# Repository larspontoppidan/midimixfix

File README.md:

# MidiMixFix

*Now open source!*

Midimixfix is a standalone MIDI processing unit with custom designed electronics and software for mixing and processing streams of MIDI.

## Features at a glance

- Two MIDI inputs and one MIDI output.
- Two pedal inputs assignable to MIDI controllers.
- All inputs can have their MIDI channels filtered, reassigned, merged or individually processed very flexibly. MIDI messages can be modified and generated.
- Midimixfix is independent of a PC. Configuration is done using the buttons and display.
- Transformation of continuous MIDI message values based on configurable curves.
- Splitting of polyphony into seperate monophonic MIDI channels for control of individual notes.
- Aftertouch processing, smoothing and reassignment to other controllers.
- Conditional processing based on triggers or keyboard split.
- Analysis of MIDI data with the MIDI logger feature.
- Save/Load of configuration presets. One preset is loaded at start up.
- Software in Midimixfix can be upgraded using the USB connection.

## Links

Read more here: https://larsee.com/blog/tag/midimixfix.html

Youtube video demonstrations:
- [Midimixfix demonstration, fixing key velocity using curve filter](https://www.youtube.com/watch?v=JRt7MXFQuEk)
- [Vibrato Pedal on a Piano? Enhancing Rachmaninoff with Midimixfix](https://www.youtube.com/watch?v=KIDRwiXo5tw)
- [Polyphonic aftertouch effects with Midimixfix channel split feature](https://www.youtube.com/watch?v=yqUHe00-khM)

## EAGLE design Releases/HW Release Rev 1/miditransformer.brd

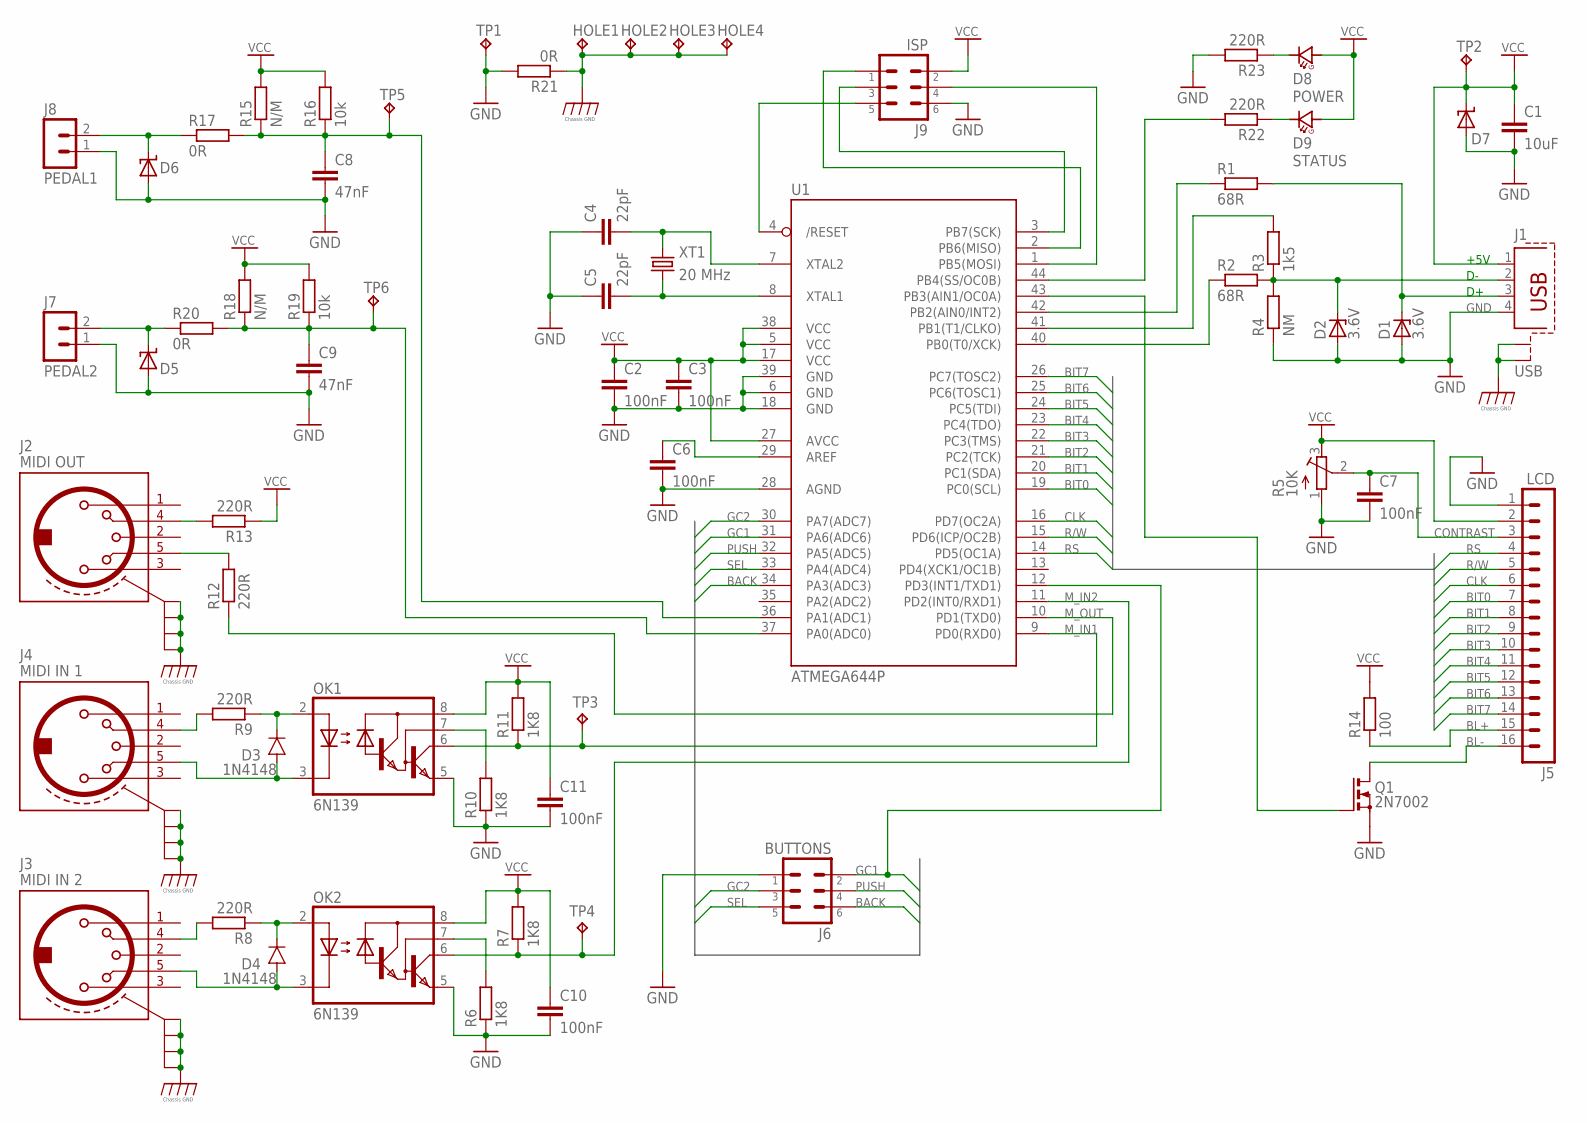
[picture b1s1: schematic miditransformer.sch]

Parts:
C1: 10uF; C1210
C2, C3, C6, C7, C10, C11: 100nF; C0805
C4, C5: 22pF; C0805
C8, C9: 47nF; C0805
D1, D2: 3.6V; DO34Z7
D3, D4: 1N4148; MINIMELF
D5, D6, D7: SUPPRESSOR-SMB; SMB
D8: POWER; LED3MM
D9: STATUS; LED3MM
HOLE1, HOLE2, HOLE3, HOLE4: HOLE_PAD; HOLE_PAD_3.2
J1: USB; PN61729-S
J2: MIDI OUT; DIN5_FEM_UNIV
J3: MIDI IN 2; DIN5_FEM_UNIV
J4: MIDI IN 1; DIN5_FEM_UNIV
J5: LCD; HDR_S_2X8
J6: BUTTONS; HDR_S_2X3
J7: PEDAL2; MOLEX_KK_HDR2_FL
J8: PEDAL1; MOLEX_KK_HDR2_FL
J9: ISP; HDR_2X3
OK1, OK2: 6N139; DIL08
Q1: 2N7002; SOT23
R1, R2: 68R; R0805
R3: 1k5; R0805
R4: NM; R0805
R5: 10K; RTRIM3339P
R6, R7, R10, R11: 1K8; R0805
R8, R9, R12, R13, R22, R23: 220R; R0805
R14: 100; 0207/7
R15, R18: N/M; R0805
R16, R19: 10k; R0805
R17, R20, R21: 0R; R0805
TP1, TP2, TP3, TP4, TP5, TP6: TPTH-15-06; TP-TH-15-06
U1: ATMEGA644P; TQFP44
XT1: 20 MHz; HC49

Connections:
BACK: J6.6, U1.34 (PA3(ADC3))
BIT0: J5.7, U1.19 (PC0(SCL))
BIT1: J5.8, U1.20 (PC1(SDA))
BIT2: J5.9, U1.21 (PC2(TCK))
BIT3: J5.10, U1.22 (PC3(TMS))
BIT4: J5.11, U1.23 (PC4(TDO))
BIT5: J5.12, U1.24 (PC5(TDI))
BIT6: J5.13, U1.25 (PC6(TOSC1))
BIT7: J5.14, U1.26 (PC7(TOSC2))
BL+: J5.15, R14.1
BL-: J5.16, Q1.3 (D)
CLK: J5.6, U1.16 (PD7(OC2A))
CONTRAST: C7.1, J5.3, R5.2 (S)
GC1: J6.2, U1.12 (PD3(INT1/TXD1)), U1.31 (PA6(ADC6))
GC2: J6.3, U1.30 (PA7(ADC7))
GND: C1.2, C2.2, C3.2, C4.1, C5.1, C6.2, C7.2, C8.2, C9.2, C10.2, C11.2, D1.A, D2.A, D5.A, D6.A, D7.A, J1.4, J5.1, J6.1, J7.1, J8.1, J9.6, OK1.5 (GND), OK2.5 (GND), Q1.2 (S), R4.1, R5.1 (E), R6.1, R10.1, R21.2, R23.2, TP1.1, U1.6 (GND), U1.18 (GND), U1.28 (AGND), U1.39 (GND)
M_IN1: OK1.6 (VO), R11.1, TP3.1, U1.9 (PD0(RXD0))
M_IN2: OK2.6 (VO), R7.1, TP4.1, U1.11 (PD2(INT0/RXD1))
M_OUT: R12.1, U1.10 (PD1(TXD0))
unnamed: D1.C, J1.3, R1.2
unnamed: D2.C, J1.2, R2.2, R3.1, R4.2
unnamed: R1.1, U1.42 (PB2(AIN0/INT2))
unnamed: R2.1, U1.40 (PB0(T0/XCK))
unnamed: C5.2, U1.8 (XTAL1), XT1.2
unnamed: R3.2, U1.41 (PB1(T1/CLKO))
unnamed: C4.2, U1.7 (XTAL2), XT1.1
unnamed: D9.C, R22.1
unnamed: OK2.7 (VB), R6.2
unnamed: J9.5, U1.4 (/RESET)
unnamed: J9.1, U1.2 (PB6(MISO))
unnamed: J9.3, U1.3 (PB7(SCK))
unnamed: J9.4, U1.1 (PB5(MOSI))
unnamed: D3.A, J4.5, OK1.3 (C)
unnamed: D4.C, OK2.2 (A), R8.1
unnamed: D8.C, R23.1
unnamed: J3.4, R8.2
unnamed: D4.A, J3.5, OK2.3 (C)
unnamed: OK1.7 (VB), R10.2
unnamed: R22.2, U1.44 (PB4(SS/OC0B))
unnamed: Q1.1 (G), U1.43 (PB3(AIN1/OC0A))
unnamed: D3.C, OK1.2 (A), R9.1
unnamed: D6.C, J8.2, R17.1
unnamed: J4.4, R9.2
unnamed: J2.4, R13.2
unnamed: J2.5, R12.2
unnamed: D5.C, J7.2, R20.1
unnamed: C6.1, U1.29 (AREF)
unnamed: C9.1, R18.1, R19.1, R20.2, TP6.1, U1.37 (PA0(ADC0))
unnamed: C8.1, R15.1, R16.1, R17.2, TP5.1, U1.36 (PA1(ADC1))
P$1: HOLE1.P$0, HOLE2.P$0, HOLE3.P$0, HOLE4.P$0, J1.S1, J1.S2, J2.PE@1 (PE), J2.PE@2 (PE), J2.PE@3 (PE), J2.PE@4 (PE), J3.PE@1 (PE), J3.PE@2 (PE), J3.PE@3 (PE), J3.PE@4 (PE), J4.PE@1 (PE), J4.PE@2 (PE), J4.PE@3 (PE), J4.PE@4 (PE), R21.1
PUSH: J6.4, U1.32 (PA5(ADC5))
R/W: J5.5, U1.15 (PD6(ICP/OC2B))
RS: J5.4, U1.14 (PD5(OC1A))
SEL: J6.5, U1.33 (PA4(ADC4))
VCC: C1.1, C2.1, C3.1, C10.1, C11.1, D7.C, D8.A, D9.A, J1.1, J5.2, J9.2, OK1.8 (VCC), OK2.8 (VCC), R5.3 (A), R7.2, R11.2, R13.1, R14.2, R15.2, R16.2, R18.2, R19.2, TP2.1, U1.5 (VCC), U1.17 (VCC), U1.27 (AVCC), U1.38 (VCC)

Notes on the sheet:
+5V

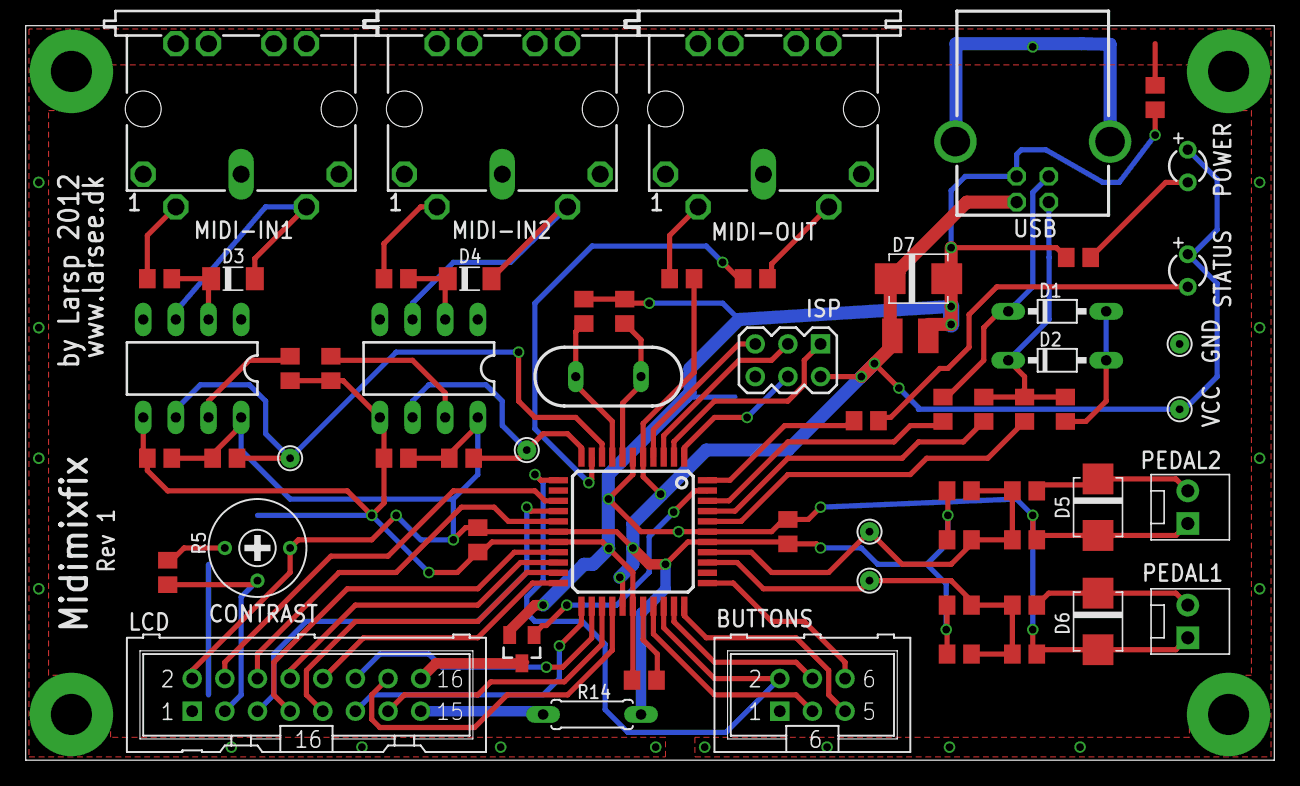
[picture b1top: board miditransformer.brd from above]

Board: 2 copper layers, 97.2 x 57.1 mm, 67 parts (0 on the bottom side), 55 nets.

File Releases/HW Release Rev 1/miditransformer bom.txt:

Partlist

Exported from miditransformer.sch at 11/18/12 11:46 AM

EAGLE Version 5.11.0 Copyright (c) 1988-2010 CadSoft

Part     Value          Device            Package          Library    Sheet

C1       10uF           C-EU_1210R        C1210            cap        1
C2       100nF          C-EU_0805R        C0805            cap        1
C3       100nF          C-EU_0805R        C0805            cap        1
C4       22pF           C-EU_0805R        C0805            cap        1
C5       22pF           C-EU_0805R        C0805            cap        1
C6       100nF          C-EU_0805R        C0805            cap        1
C7       100nF          C-EU_0805R        C0805            cap        1
C8       22nF           C-EU_0805R        C0805            cap        1
C9       22nF           C-EU_0805R        C0805            cap        1
C10      100nF          C-EU_0805R        C0805            cap        1
C11      100nF          C-EU_0805R        C0805            cap        1
D1       3.6V           ZENER-DIODEDO34-7 DO34Z7           _newbylars 1
D2       3.6V           ZENER-DIODEDO34-7 DO34Z7           _newbylars 1
D3       1N4148         1N4148MINIMELF    MINIMELF         _newbylars 1
D4       1N4148         1N4148MINIMELF    MINIMELF         _newbylars 1
D5                      SUPPRESSOR-SMB    SMB              _newbylars 1
D6                      SUPPRESSOR-SMB    SMB              _newbylars 1
D7                      SUPPRESSOR-SMB    SMB              _newbylars 1
D8       POWER          LTL-1CHG          LED3MM           leds       1
D9       STATUS         LTL-1CHG          LED3MM           leds       1
HOLE1    HOLE_PAD       HOLE_PAD          HOLE_PAD_3.2     _newbylars 1
HOLE2    HOLE_PAD       HOLE_PAD          HOLE_PAD_3.2     _newbylars 1
HOLE3    HOLE_PAD       HOLE_PAD          HOLE_PAD_3.2     _newbylars 1
HOLE4    HOLE_PAD       HOLE_PAD          HOLE_PAD_3.2     _newbylars 1
J1       USB            PN61729-S         PN61729-S        _newbylars 1
J2       MIDI OUT       DIN5_FEMALE_PCB   DIN5_FEM_UNIV    _newbylars 1
J3       MIDI IN 2      DIN5_FEMALE_PCB   DIN5_FEM_UNIV    _newbylars 1
J4       MIDI IN 1      DIN5_FEMALE_PCB   DIN5_FEM_UNIV    _newbylars 1
J5       LCD            HEADER2X8LS       HDR_S_2X8        con-head   1
J6       BUTTONS        HEADER2X3S        HDR_S_2X3        con-head   1
J7       PEDAL2         HEADER1X2KK       MOLEX_KK_HDR2_FL con-head   1
J8       PEDAL1         HEADER1X2KK       MOLEX_KK_HDR2_FL con-head   1
J9       ISP            HEADER2X3         HDR_2X3          _newbylars 1
OK1      6N139          6N138DIL08        DIL08            _newbylars 1
OK2      6N139          6N138DIL08        DIL08            _newbylars 1
Q1       2N7002         2N7002            SOT23            fet        1
R1       82R            R-EU0805          R0805            _newbylars 1
R2       82R            R-EU0805          R0805            _newbylars 1
R3       2k2            R-EU0805          R0805            _newbylars 1
R4       4k7            R-EU0805          R0805            _newbylars 1
R5                      R-TRIMM           RTRIM3339P       _newbylars 1
R6       1K8            R-EU0805          R0805            _newbylars 1
R7       1K8            R-EU0805          R0805            _newbylars 1
R8       220R           R-EU0805          R0805            _newbylars 1
R9       220R           R-EU0805          R0805            _newbylars 1
R10      1K8            R-EU0805          R0805            _newbylars 1
R11      1K8            R-EU0805          R0805            _newbylars 1
R12      220R           R-EU0805          R0805            _newbylars 1
R13      220R           R-EU0805          R0805            _newbylars 1
R14      100            R-EULEADED-7.5    0207/7           _newbylars 1
R15      N/M            R-EU0805          R0805            _newbylars 1
R16      10k            R-EU0805          R0805            _newbylars 1
R17      0R             R-EU0805          R0805            _newbylars 1
R18      N/M            R-EU0805          R0805            _newbylars 1
R19      10k            R-EU0805          R0805            _newbylars 1
R20      0R             R-EU0805          R0805            _newbylars 1
R21      0R             R-EU0805          R0805            _newbylars 1
R22      220R           R-EU0805          R0805            _newbylars 1
R23      220R           R-EU0805          R0805            _newbylars 1
TP1      TPTH-15-06     TPTH-15-06        TP-TH-15-06      _newbylars 1
TP2      TPTH-15-06     TPTH-15-06        TP-TH-15-06      _newbylars 1
TP3      TPTH-15-06     TPTH-15-06        TP-TH-15-06      _newbylars 1
TP4      TPTH-15-06     TPTH-15-06        TP-TH-15-06      _newbylars 1
TP5      TPTH-15-06     TPTH-15-06        TP-TH-15-06      _newbylars 1
TP6      TPTH-15-06     TPTH-15-06        TP-TH-15-06      _newbylars 1
U1       ATMEGA644P     ATMEGA644P        TQFP44           avr-mcu    1
XT1      20 MHz         XTAL_HC49         HC49             crystal    1

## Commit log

2012-08-09 Unmodified USBasploader.2010-07-27 commit
2012-08-09 Configured for ATmega32 on TP-USB-KEYB. Doesn't work!
2012-08-09 Bootloader works!
2012-11-18 Bootloader configured for ATmega644P on midimixfix, seems to work!
2013-01-12 First commit. Basic functionality including midilogger and block filter works without problems
2013-01-12 Curve filter implemented. Works great! Plus other minor adjustments.
2013-01-13 Preset save / load implemented.
2013-01-13 Presets modified indication. Bugfix in curvefilter and adjustments
2013-01-19 New generate msg filter implemented! OBS Currently refactoring into new coding style...
2013-01-19 Blockfilter and curvefilter simplified to not have Manage... Add/Remove but filtercount in ()
2013-02-24 100 Hz tick implemented and tested, works
2013-02-24 First shot at superdelay. Menu not implemented. Works, though algorithm does not handle multiple presses on same key well...
2013-03-02 Superdelay reimplemented. New approach. Still needs final adjustments. No menu yet
2013-03-03 Superdelay: Swing delay implemented! Other miner improvements
2013-03-14 Tap delay works in superdelay
2013-03-16 Menu added to superdelay and further fixes on superdelay. Works pretty well. Format print function implemented
2013-03-16 Block filter completely rewritten. Now supports block and mapping in all sorts of ways. Works. Need a little refactoring and renaming
2013-05-09 Now compiles with maximum warning level on GCC: -Wextra and -pedantic
2013-05-09 Coding style refactoring in progress. Renaming...
2013-05-09 Refactoring: midimessage split into midigenerics and midimessage
2013-05-09 Coding style refactoring in progress. Renaming
2013-05-09 Coding style refactoring. Renaming DONE!
2013-05-11 Slightly more refactoring. Pedals implemented!
2013-05-12 Pedal mostly works
2013-05-12 Profiling measurements
2013-05-19 Attempt at fixing chip erase. Doesn't seem to work though. Makefile fixed so fuses can be set on new AVRs by slowing down ISP
2013-05-19 Unmodified USBaspLoader.2012-12-08 loaded
2013-05-19 Bootloader works with HAVE_CHIP_ERASE to 0. It doesn't appear to work. Bootloader condition now active.
2013-05-20 Pedal config works
2013-05-20 Hardware test implemented
2013-05-20 Bootloader behaviour changed so bootloadercondition only needs to be true at startup
2013-05-20 Hardware test more or less reimplemented. Is complete now!
2013-05-20 Bootloadercondition now with glitch filter.
2013-05-20 Added tag Deployed for changeset 375cde8a17af
2013-07-07 Jul 7 2013 release. Compiles with avr-gcc 4.7.2, a number of bugs fixed
2013-09-05 First shot at polysplit function, works! but no menu
2013-10-06 HUGE refactoring. New menu and processing principle on it's way
2013-10-07 Filter add remove reorder appearently works!
2013-10-07 Add remove reorder works 100% now. filtermenu implemented, seems to work
2013-10-07 Midilog via midilogmenu implemented
2013-10-13 Menu interfaces moved to PROGMEM, 72 bytes ram saved
2013-10-13 Menu interface changed to not use get function for the menuInterface_t struct. The same principle will be applied to filters as it is more efficient.
2013-10-17 New function pointer based filter architecture implemented
2013-10-17 Send with running status works! Fixes to handling of sys.realtime and midilog. Special NoteOff conversion.
2013-10-18 Route channel filter implemented. Various bugfixes.
2013-10-19 Pedals, set channel, transpose all implemented
2013-10-20 UI Menu implementation changed to use update requests instead of convoluted calling of ui_menuDrawItem. Current program:19284 ram:784
2013-10-20 More sensible UI BACK behaviour and message screen implemented
2013-10-20 Live update of menu items now possible in filters and used by Pedals
2013-10-20 filtermenu bugfix
2013-10-20 Aboutscreen added capable of showing registered errors
2013-10-29 Curvefilter implemented
2013-10-29 Curvefilter bugfixed
2013-11-03 Generatemsg implemented. Presetstorage implemented, needs finetuning.
2013-11-03 Preset saving/loading improved. Filter UIDs defined better.
2013-12-31 Improved quadrature decoder with noise rejection
2014-01-19 Simple poly split implemented
2014-01-19 Modify controller extended to handle other than CC
2014-01-19 THIS IS v1.0. Smoothing added to PolySplit.
2014-03-07 Route msg filter implemented
2014-03-07 New unified route / duplicate filter implemented. Works!
2014-03-07 V1.1 Release. Generate msg filter big improvement. Bug fix, midiproc_handleTick wasn't called!
2014-05-04 Serious bug fixes! Duplicate filter numbering error. Similar named Instance[] vars were not static!
2014-05-06 AT Smooth filter implemented
2014-05-06 New smoothing algorithm
2014-05-07 Resetter implemented. Preset save too big error handler.
2014-05-07 Minor gui fixes
2014-05-07 THIS IS: MIDIMIXFIX v1.02
2014-05-16 Control noteon filter implemented
2014-05-16 Key split route filter implemented
2014-05-16 Conditional route implemented
2014-05-16 About screen enhanced with data about config
2014-05-17 STILL: v1.02 User interface text improved
2014-05-26 Release: v1.02
2019-02-16 update tags
2019-02-16 Convert NoteOn vel. 0 to NoteOff function moved to earlier on processing chain
2019-02-16 Coding Style document added
2019-02-16 Eclipse project files added
2019-02-16 doc folder .gitignore added and various reorganization
2019-02-16 bootloder: Missing files added
2019-02-16 Releases folder added with all SW and HW releases
2019-02-16 Funny old sw architecture draft doc added
2019-02-16 HW folder added and hardware rev. 1 pictures
2019-02-16 Readme and License added
